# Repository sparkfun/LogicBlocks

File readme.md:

LogicBlocks Kit
============================

[  
*LogicBlocks Kit (KIT-11006)*](https://www.sparkfun.com/products/11006)

LogicBlocks allow you to play with logic gates by literally plugging one into another and watching the progression of an input to an output! Each LogicBlock represents a different logic function: the NOT block is a simple inverter, where the output is the opposite of the input. The AND block will only output a 1 if both of the inputs are 1. The OR block will output a 1 if either of the inputs are 1. There are also input blocks and splitter blocks.

Repository Contents
-------------------
* **/Hardware** - All Eagle design files (.brd, .sch)

License Information
-------------------
The hardware is released under [Creative Commons ShareAlike 4.0 International](https://creativecommons.org/licenses/by-sa/4.0/).

Distributed as-is; no warranty is given.

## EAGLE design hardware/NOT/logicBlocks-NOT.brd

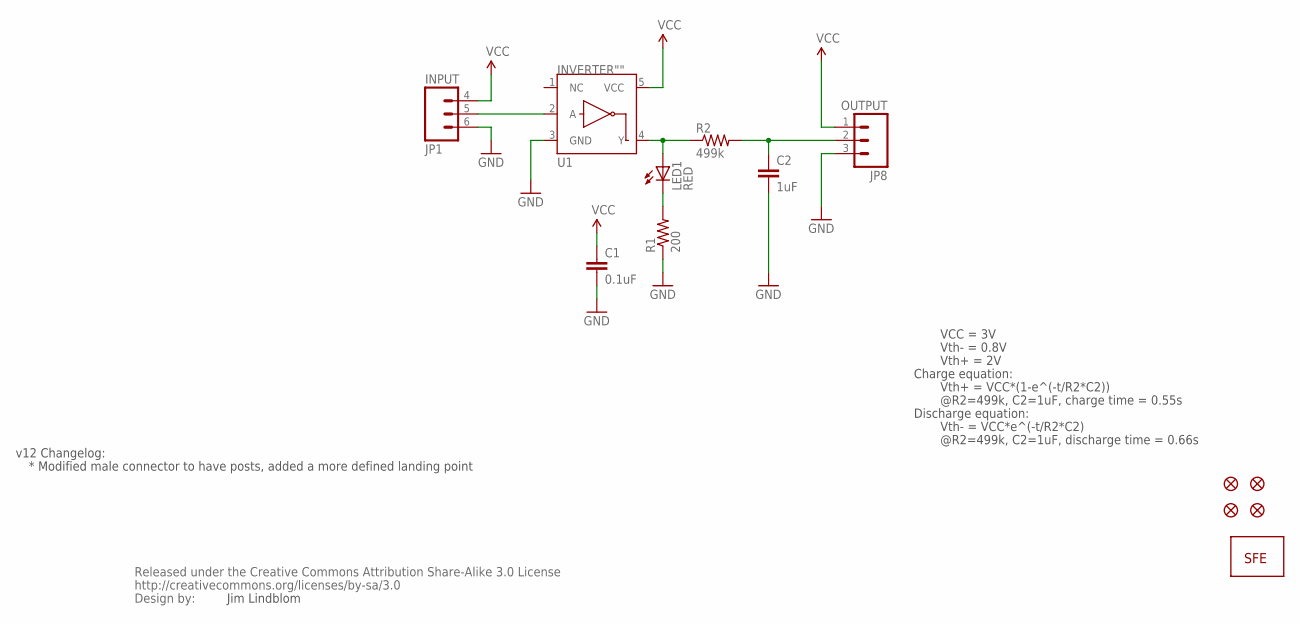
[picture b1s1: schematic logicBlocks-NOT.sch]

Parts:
C1: 0.1uF; 0402-CAP
C2: 1uF; 0402-CAP
FID1, FID2, FID3, FID4: FIDUCIAL1X2; FIDUCIAL-1X2
JP1: INPUT; 1X03-SMD-FEMALE
JP4: LOGO-SFESK; SFE-LOGO-FLAME
JP8: OUTPUT; 1X03_SMD_RA_MALE_POST
LED1: RED; LED-1206
R1: 200; 0402-RES
R2: 499k; 0402-RES
U1: INVERTER""; SC70
U$2: CREATIVE_COMMONS

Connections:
GND: C1.2, C2.2, JP1.6 (3), JP8.3, R1.1, U1.3 (GND)
unnamed: LED1.C, R1.2
unnamed: JP1.5 (2), U1.2 (A)
unnamed: LED1.A, R2.1, U1.4 (Y)
unnamed: C2.1, JP8.2, R2.2
VCC: C1.1, JP1.4 (1), JP8.1, U1.5 (VCC)

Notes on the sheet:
Jim Lindblom
Charge equation:
Vth+ = VCC*(1-e^(-t/R2*C2))
Vth+ = 2V
Vth- = 0.8V
@R2=499k, C2=1uF, charge time = 0.55s
Discharge equation:
Vth- = VCC*e^(-t/R2*C2)
@R2=499k, C2=1uF, discharge time = 0.66s
v12 Changelog:
* Modified male connector to have posts, added a more defined landing point
VCC = 3V

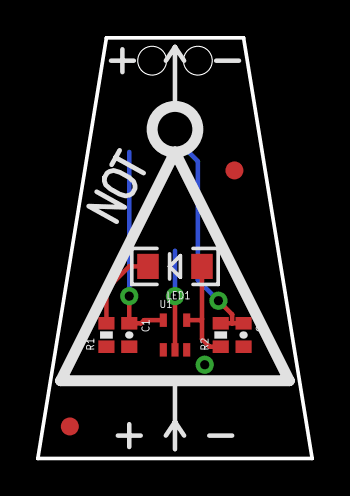
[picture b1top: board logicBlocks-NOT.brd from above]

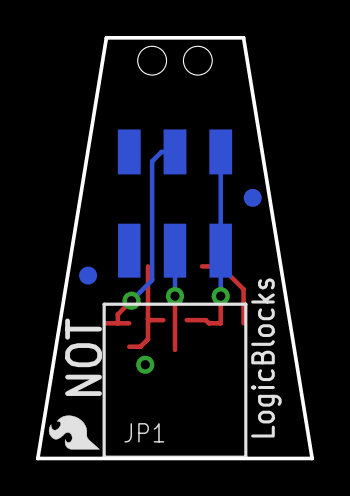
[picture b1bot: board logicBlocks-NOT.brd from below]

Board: 2 copper layers, 15.2 x 23.4 mm, 14 parts (5 on the bottom side), 6 nets.

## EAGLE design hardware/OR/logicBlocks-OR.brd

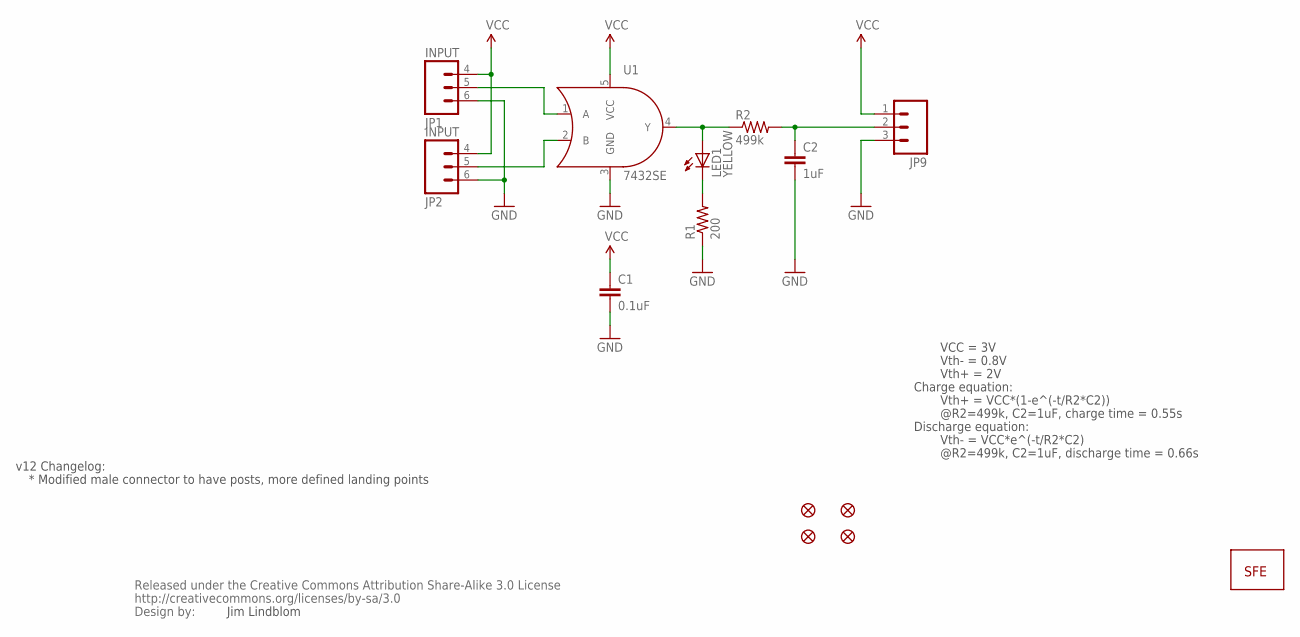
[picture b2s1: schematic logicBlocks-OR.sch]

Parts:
C1: 0.1uF; 0402-CAP
C2: 1uF; 0402-CAP
JP1, JP2: INPUT; 1X03-SMD-FEMALE
JP4: LOGO-SFESK; SFE-LOGO-FLAME
JP5, JP6, JP7, JP8: FIDUCIALUFIDUCIAL; MICRO-FIDUCIAL
JP9: M03SMD_RA_MALE_POST; 1X03_SMD_RA_MALE_POST
LED1: YELLOW; LED-1206
R1: 200; 0402-RES
R2: 499k; 0402-RES
U1: 7432SE; SOT353
U$2: CREATIVE_COMMONS

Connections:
GND: C1.2, C2.2, JP1.6 (3), JP2.6 (3), JP9.3, R1.1, U1.3 (GND)
unnamed: LED1.C, R1.2
unnamed: JP1.5 (2), U1.1 (A)
unnamed: JP2.5 (2), U1.2 (B)
unnamed: LED1.A, R2.1, U1.4 (Y)
unnamed: C2.1, JP9.2, R2.2
VCC: C1.1, JP1.4 (1), JP2.4 (1), JP9.1, U1.5 (VCC)

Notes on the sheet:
Jim Lindblom
Charge equation:
Vth+ = VCC*(1-e^(-t/R2*C2))
Vth+ = 2V
Vth- = 0.8V
@R2=499k, C2=1uF, charge time = 0.55s
Discharge equation:
Vth- = VCC*e^(-t/R2*C2)
@R2=499k, C2=1uF, discharge time = 0.66s
v12 Changelog:
VCC = 3V
* Modified male connector to have posts, more defined landing points

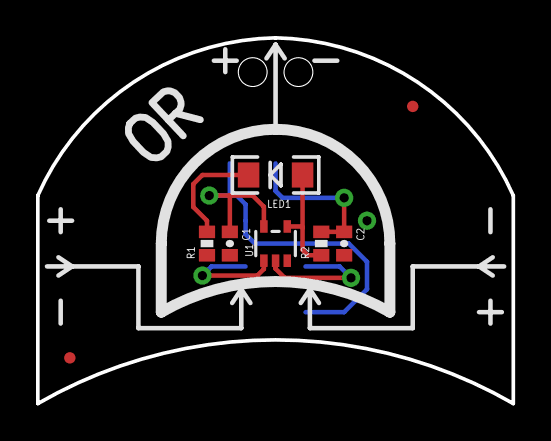
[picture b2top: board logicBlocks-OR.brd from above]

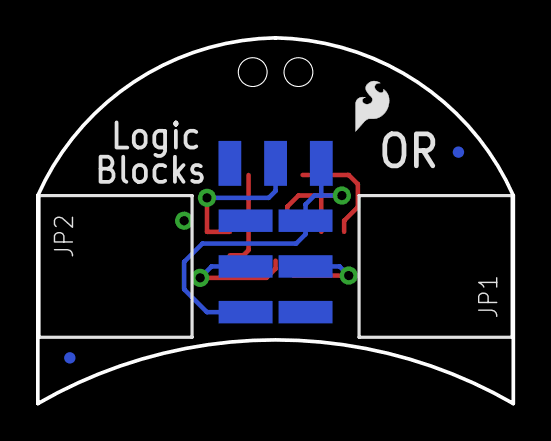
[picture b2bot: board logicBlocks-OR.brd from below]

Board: 2 copper layers, 26.4 x 20.3 mm, 15 parts (6 on the bottom side), 7 nets.

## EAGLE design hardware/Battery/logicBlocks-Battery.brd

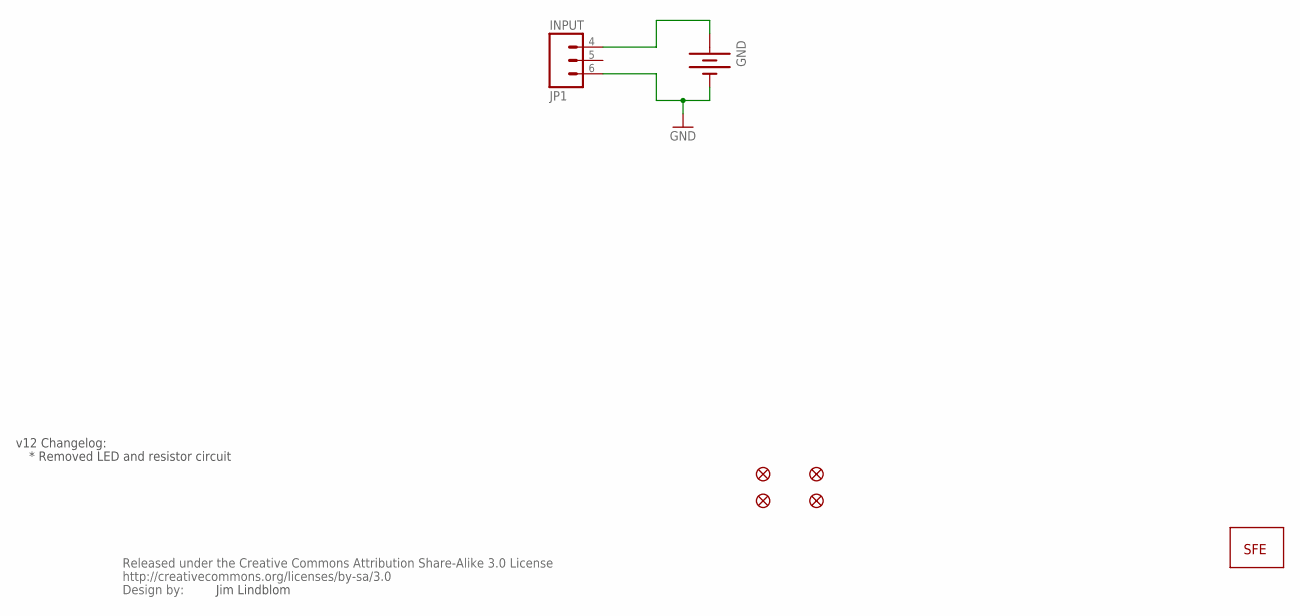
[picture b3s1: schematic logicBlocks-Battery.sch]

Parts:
GND: BATTERY20MM_4LEGS; BATTCON_20MM_4LEGS
JP1: INPUT; 1X03-SMD-FEMALE
JP3: LOGO-SFESK; SFE-LOGO-FLAME
JP4, JP5, JP6, JP7: FIDUCIALUFIDUCIAL; MICRO-FIDUCIAL
U$2: CREATIVE_COMMONS

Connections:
GND: GND.2 (-), JP1.6 (3)
VCC: GND.1 (+), JP1.4 (1)

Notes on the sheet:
Jim Lindblom
v12 Changelog:
* Removed LED and resistor circuit

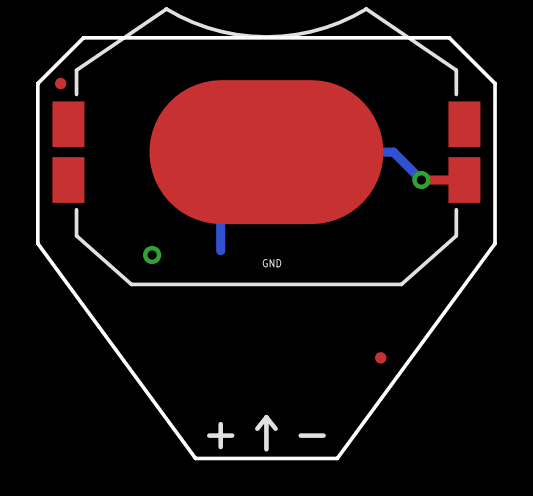
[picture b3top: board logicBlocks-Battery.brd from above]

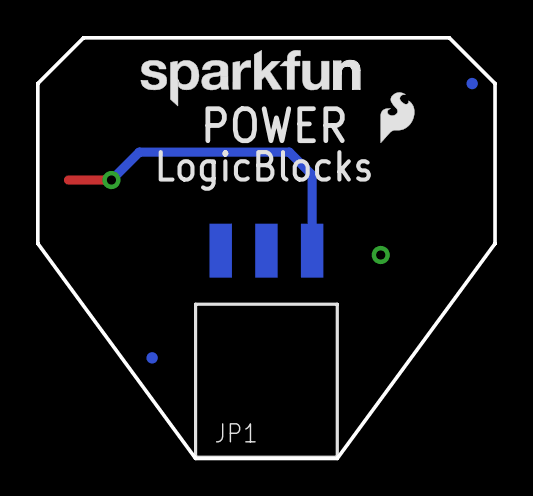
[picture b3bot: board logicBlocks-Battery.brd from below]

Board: 2 copper layers, 25.4 x 23.4 mm, 9 parts (5 on the bottom side), 2 nets.

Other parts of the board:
JP2: LOGO-SFENW2; SFE-NEW-WEB

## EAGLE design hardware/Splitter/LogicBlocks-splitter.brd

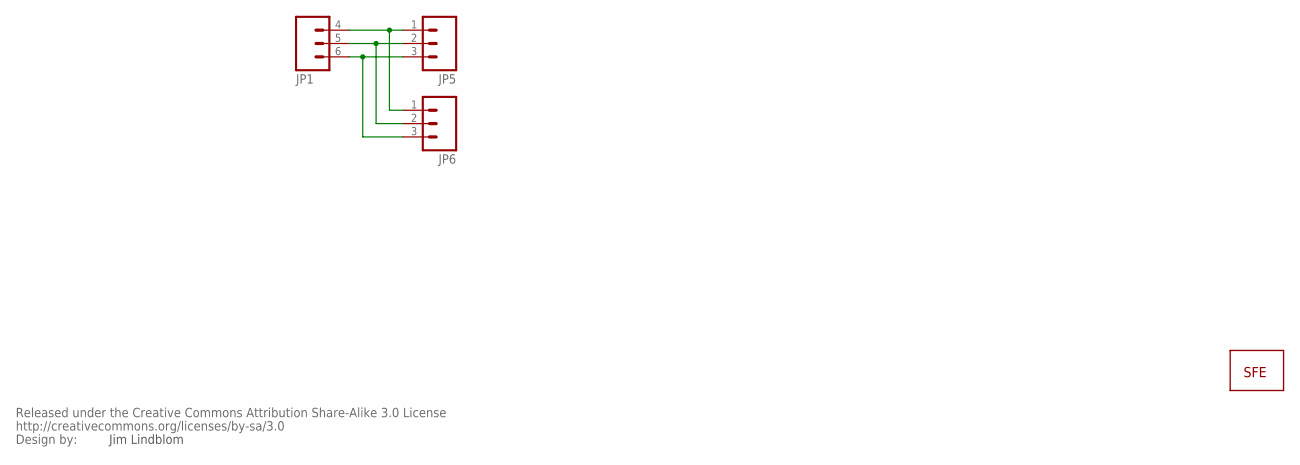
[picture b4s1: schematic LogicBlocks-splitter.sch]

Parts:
JP1: M03SMD-RA-FEMALE; 1X03-SMD-FEMALE
JP4: LOGO-SFESK; SFE-LOGO-FLAME
JP5, JP6: M03SMD_RA_MALE_POST; 1X03_SMD_RA_MALE_POST
U$1: CREATIVE_COMMONS

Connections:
GND: JP1.6 (3), JP5.3, JP6.3
S: JP1.5 (2), JP5.2, JP6.2
VCC: JP1.4 (1), JP5.1, JP6.1

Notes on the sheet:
Jim Lindblom

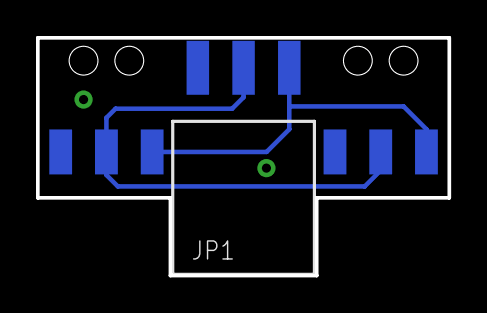
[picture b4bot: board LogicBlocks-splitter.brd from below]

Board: 2 copper layers, 22.9 x 13.2 mm, 5 parts (3 on the bottom side), 3 nets.

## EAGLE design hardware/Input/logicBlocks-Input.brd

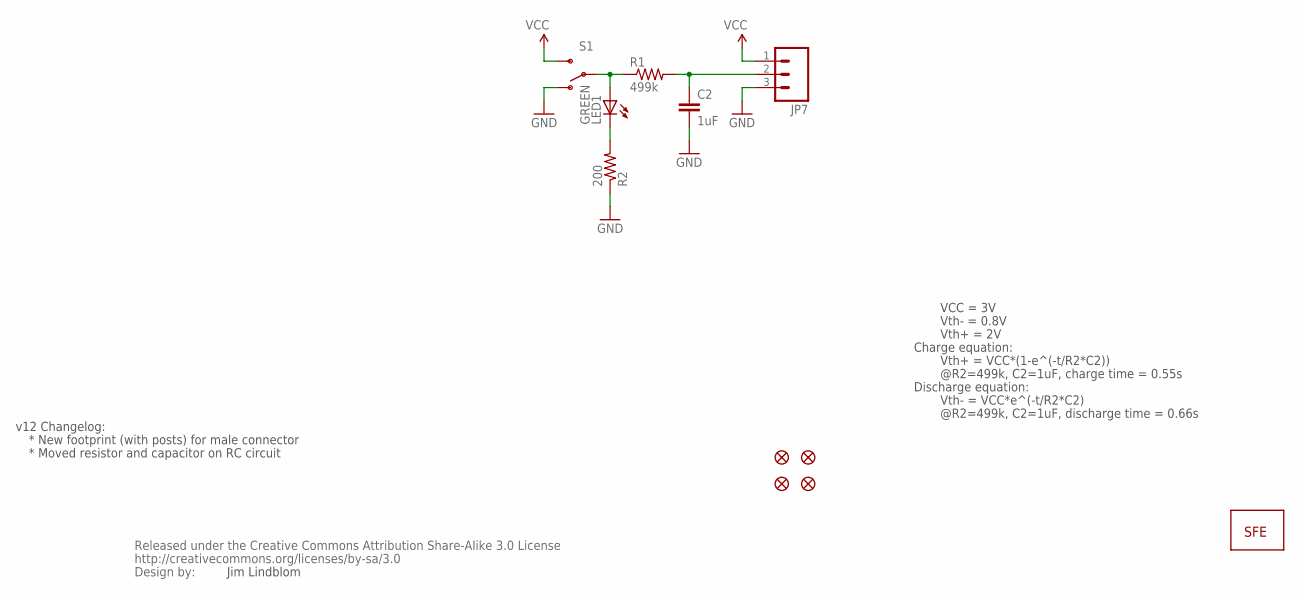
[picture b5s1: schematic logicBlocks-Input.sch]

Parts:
C2: 1uF; 0402-CAP
JP2: LOGO-SFESK; SFE-LOGO-FLAME
JP3, JP4, JP5, JP6: FIDUCIALUFIDUCIAL; MICRO-FIDUCIAL
JP7: M03SMD_RA_MALE_POST; 1X03_SMD_RA_MALE_POST
LED1: GREEN; LED-1206
R1: 499k; 0402-RES
R2: 200; 0402-RES
S1: SWITCH-SPSTSMD; AYZ0202
U$2: CREATIVE_COMMONS

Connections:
GND: C2.2, JP7.3, R2.1, S1.1 (O)
unnamed: C2.1, JP7.2, R1.2
unnamed: LED1.A, R1.1, S1.2
unnamed: LED1.C, R2.2
VCC: JP7.1, S1.3 (S)

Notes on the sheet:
Jim Lindblom
Charge equation:
Vth+ = VCC*(1-e^(-t/R2*C2))
Vth+ = 2V
Vth- = 0.8V
@R2=499k, C2=1uF, charge time = 0.55s
Discharge equation:
Vth- = VCC*e^(-t/R2*C2)
@R2=499k, C2=1uF, discharge time = 0.66s
v12 Changelog:
VCC = 3V
* New footprint (with posts) for male connector
* Moved resistor and capacitor on RC circuit

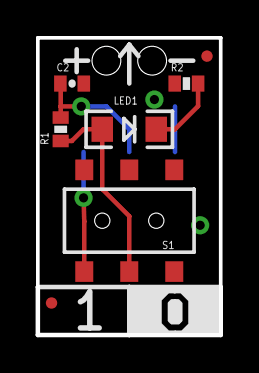
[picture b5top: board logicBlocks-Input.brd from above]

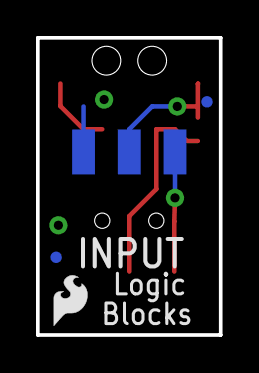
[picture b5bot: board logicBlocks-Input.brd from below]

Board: 2 copper layers, 10.2 x 16.5 mm, 12 parts (5 on the bottom side), 5 nets.

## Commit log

2013-08-19 v11 (currently live) of all boards
    Also initial commit of readme.md
2013-08-19 v12 of all boards -- Male headers w/ posts
2014-09-24 changed to regular fiducials
2014-11-05 Updating README, adding .gitignore

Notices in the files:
parts and their libraries:
SparkFun: Released under the Creative Commons Attribution Share-Alike 3.0 License
SparkFun: http://creativecommons.org/licenses/by-sa/3.0
SparkFun-Connectors: Licensing: CC v3.0 Share-Alike You are welcome to use this library for commercial purposes.
